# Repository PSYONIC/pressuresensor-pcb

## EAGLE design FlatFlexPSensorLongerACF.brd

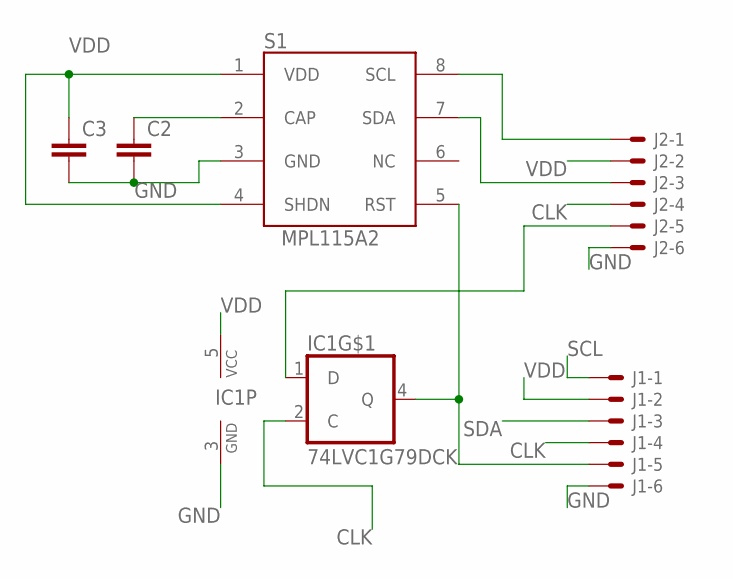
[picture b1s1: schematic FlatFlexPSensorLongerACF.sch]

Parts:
C2, C3: CC0402; C0402
IC1: 74LVC1G79DCK; SC70-5
J1, J2: XF2L-0625-1
S1: MPL115A2; LGA8

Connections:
CLK: IC1.2 (C), J1.4, J2.4
D: IC1.1 (D), J2.5
GND: C2.2, C3.2, IC1.3 (GND), J1.6, J2.6, S1.3 (GND)
unnamed: C2.1, S1.2 (CAP)
Q: IC1.4 (Q), J1.5, S1.5 (RST)
SCL: J1.1, J2.1, S1.8 (SCL)
SDA: J1.3, J2.3, S1.7 (SDA)
VDD: C3.1, IC1.5 (VCC), J1.2, J2.2, S1.1 (VDD), S1.4 (SHDN)

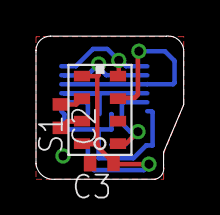
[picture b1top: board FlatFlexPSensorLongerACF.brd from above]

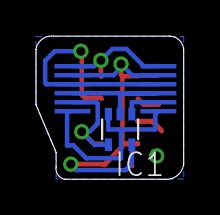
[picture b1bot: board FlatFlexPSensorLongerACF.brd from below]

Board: 2 copper layers, 8.2 x 8.0 mm, 6 parts (3 on the bottom side), 8 nets.

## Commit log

2016-10-07 first
    first commit of the pressure sensor board m8 hi how are you
